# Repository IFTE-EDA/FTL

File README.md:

## Notice

This program is currently in development state. No documentation or support is available.
But this is hopefully going to change in the future (:

#### FTL
FTL (*"Fold the line"*) is a program developed to turn flat circuit layouts done in KiCad into 3D models and bend them.
The exported geometries can be used to do simulations, measure dimensions, design enclosures etc.

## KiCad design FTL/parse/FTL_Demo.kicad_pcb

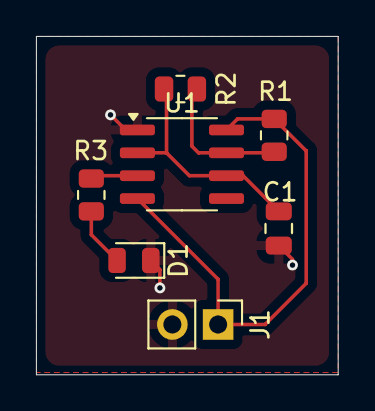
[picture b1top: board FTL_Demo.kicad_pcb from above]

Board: 2 copper layers, 16.8 x 18.8 mm, 7 parts (0 on the bottom side), 6 nets.

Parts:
C1: 10u; C_0805_2012Metric
D1: LED; LED_0805_2012Metric
J1: Conn_01x02_Pin; PinHeader_1x02_P2.54mm_Vertical
R1, R2: 100k; R_0805_2012Metric
R3: 1k; R_0805_2012Metric
U1: NE555D; SOIC-8_3.9x4.9mm_P1.27mm

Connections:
+5V: J1.1, R1.1, U1.4 (R), U1.8 (VCC)
GND: C1.2, D1.1 (K), J1.2, U1.1 (GND)
unnamed: D1.2 (A), R3.2
unnamed: R1.2, R2.1, U1.7 (DIS)
unnamed: R3.1, U1.3 (Q)
unnamed: C1.1, R2.2, U1.2 (TR), U1.6 (THR)

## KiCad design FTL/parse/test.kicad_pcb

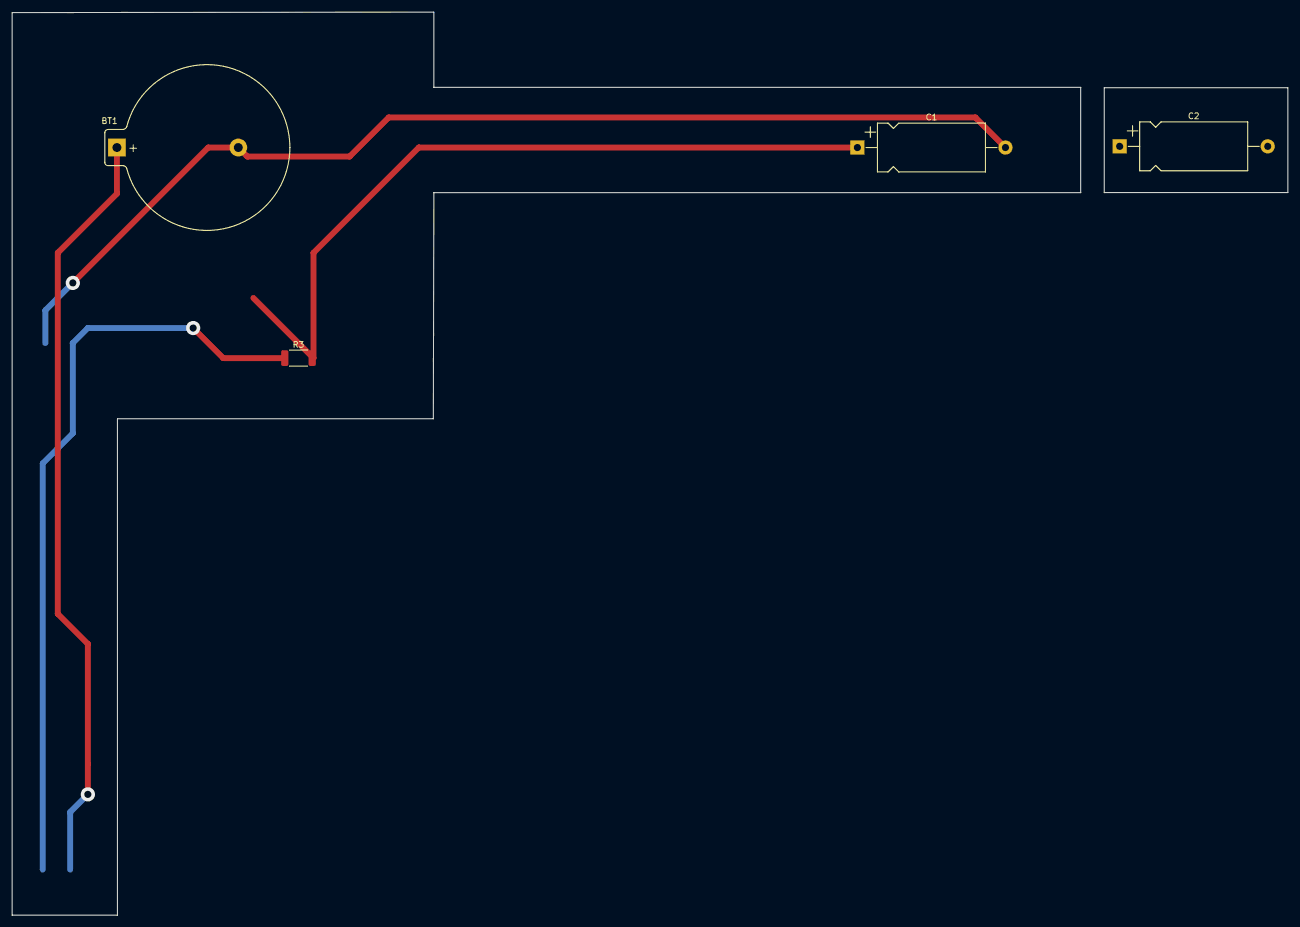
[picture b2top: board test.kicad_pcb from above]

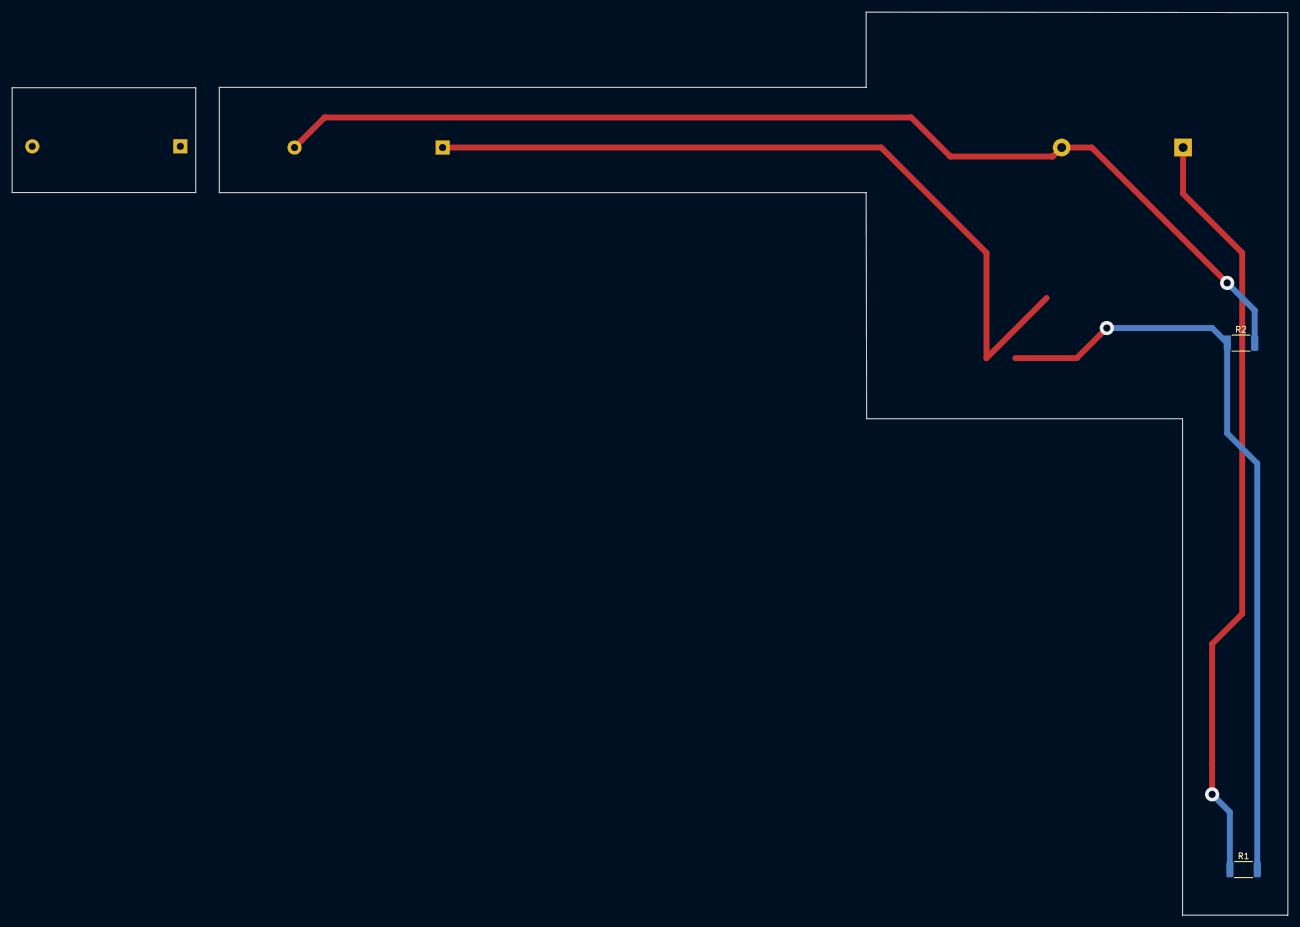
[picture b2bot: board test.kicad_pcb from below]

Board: 2 copper layers, 180.4 x 152.5 mm, 6 parts (2 on the bottom side), 4 nets.

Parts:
BT1: Battery_Cell; BatteryHolder_Keystone_105_1x2430
C1, C2: C; CP_Axial_L18.0mm_D8.0mm_P25.00mm_Horizontal
R1, R2, R3: R; R_2010_5025Metric

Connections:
unnamed: BT1.1 (+), R1.1
unnamed: BT1.2 (-), C1.2, R2.2
unnamed: C1.1, R3.2
unnamed: R1.2, R2.1, R3.1

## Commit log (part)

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2023-09-26 Update .gitlab-ci.yml file
2023-09-26 Implement transformation testing via pytest
2023-09-26 remove path manager test
2023-09-26 Daily
2023-09-26 path adress update
2023-09-26 path update
2023-09-27 Update paths
2023-09-27 Correct Path
2023-09-27 add tox
2023-09-27 Tox update
2023-09-27 Update tox
2023-09-28 Break tests
2023-09-28 Fix test
2023-09-28 Fix test data
2023-09-28 Add test debug data
2023-09-28 Update testing
2023-09-28 Fix testing
2023-09-28 Fix tests
2023-09-29 update junit suite names
2023-09-29 test
2023-09-29 tox update flake8
2023-09-29 Add flake8 functionality
2023-09-29 Update pathmanager test to pathlib
2023-09-29 fix flake8 & coverage
2023-09-29 update coverage testing
2023-10-04 Restructure the project
    Implement testing via pytest and tox
    directory structure change
    Gitlab CI
    Test coverage
    Testing data
    Bugfixing
2023-10-04 Add testing for FileParser.calculate_assignments()
2023-10-04 Fix testing, add pytest-order
2023-10-30 Remove PyQt5 dependency
2023-11-27 Done. Move to dev later.
2023-12-12 Fix 'Self' import; will correct typing later. TODO!
2023-12-12 Fix shapely-affinity problem
2024-02-22 Start Vedo Fix
2024-02-26 Initial
2024-07-25 Reorganization
2024-07-26 Add test
2024-07-26 Add Tests for FPCLayer
2024-07-26 Correct whitespace at file end
2024-07-26 Correct tox.ini
2024-07-26 Change pytest path
2024-07-26 Add Material Test
2024-07-29 Add Geometry classes
2024-07-29 Add Tests for Geometry classes
2024-07-29 Annotate class
2024-07-29 Add 3D Geom functions
2024-07-29 Add 3D Geom tests
2024-07-29 Remove v.show() causing tests to fail in headless mode
2024-07-29 Integrate nested Geom2D into Geom3D
2024-08-01 Migrate Geom2D.polygons to shapely
2024-08-01 Tidy up fcad_pcb
2024-08-01 Add support for circles
2024-08-01 Remove MainWindow-Dependency
2024-08-02 Correct FTLGeom2D.make_compound()
2024-08-02 Add class method get_circle()
2024-08-02 Correct z shift for extrusion
2024-08-02 Correct FTLGeom2D.get_circle() method
2024-08-06 Add support for: - creating rectangles - rotation - cutouts
2024-08-06 Add uspport for ellipses
2024-08-06 restructure
2024-08-07 Add support for 'roundrect' shapes
2024-08-07 Reorder
2024-08-07 Add support for arcs
2024-08-07 Extend "add_line" to support linestrings
2024-08-07 Fix FTLGeom2D.plot() for displaying overlapping polygons
2024-08-08 Remove debug outputs
2024-08-08 Add logger class with auto-indenting Mixin
2024-08-08 Add KiCAD SEXP parsing module from realthunder
2024-08-09 Test files for kicad parser
2024-08-09 Add layer list, prepare structured parsing
2024-08-09 Fix polygon creation from list + add tests
2024-08-12 Add test file for KiCAD rendering
2024-08-12 Implement layered rendering for parts and vias
2024-08-12 Implement possibility to give titles for FTLGeom2D plots
2024-08-12 Imnplement drilling
2024-08-13 Imnplement drilling to pads, utility< functions in KiCADStackupManager
2024-08-13 Make methods daisy-chainable
2024-08-13 Add tests for KiCADStackupManager
2024-08-13 Tidy up, correct rendering mistakes with single elements
2024-08-13 Add support for symbolic arcs
2024-08-13 Fix arc drawing
2024-08-14 Add Zone support
2024-08-15 Add functions to orient polys before adding
2024-08-15 Implement algorithm for poly conversion (KiCAD->Shapely)
2024-08-15 Change new layer names to "Unnamed Layer"
2024-08-20 Add colors
2024-08-20 Fix rendering problems with missing vertices
2024-08-20 Fix vertex lists
2024-08-21 Change imports to fix tests
2024-08-22 Add module
2024-08-22 Change imports
2024-08-22 Change path
2024-08-22 Update pythonpath
2024-08-22 Fix testcase
2024-08-22 Remove VMeshTools submodule
2024-08-22 remove fcad_pcb_ftl
2024-08-22 Change tox pythonpath
2024-08-22 Exclude submodules from linter
2024-08-22 Exclude .tox from linter
2024-08-27 Refactor Geometry classes, add ABC
2024-08-27 Add ABC for 3D Geometry
2024-08-27 Move tests
2024-08-27 Add GMSHGeometry and test suite; Implement Polygons, Rectangles and circles
2024-08-27 Update requirements to GMSH
2024-08-27 Install libglu1
2024-08-28 Install gmsh
2024-08-28 Install libglu1-mesa
2024-08-28 Update image
2024-08-28 Remove post-build libglu1-mesa install
2024-08-28 Implement ellipses and RoundedRects
2024-08-28 Implement Ellipses & RoundedRects
2024-08-28 Implement Lines
2024-08-28 Implement Arcs
2024-08-28 Implement Cutouts
2024-08-28 Cleanup, Implement Translation
2024-08-28 Implement Rotation
2024-08-28 Implement Extrusion
2024-08-29 Implement unfused extruding + tests
2024-08-29 Implement GMSHGeom3D tests and len() for 2D and 3D geoms
2024-08-29 Improve Object adding + implement _dimtags
2024-08-29 Add dimension parameter to GMSHGeom2D.render()
2024-09-02 Implement GMSHGeom2D.copy() and selective layer rendering
2024-09-02 Make GMSHGeom2D.plot() only show contained geometries
2024-09-02 Fix rounded rect rendering
2024-09-03 Fix KiCADParser for GMSHGeom2D
2024-09-03 Add status message argument to GMSHGeom2D.plot()
2024-09-03 Implement 3D compounds
2024-09-04 Implement setting visibility
2024-09-05 Mesh fragmenting test
2024-10-01 Fix node orientation for zones
2024-10-01 New testing file
2024-10-01 Add new test file
2024-10-02 Enable gr_line and gr_arc rendering and filling the "Edge.Cuts" layer
2024-10-02 Add new testing file
2024-10-07 Add Implement bulging to comply with DXF files
2024-10-08 Correct typo
2024-10-08 Generate test files for dxf
2024-10-08 Add testing for DXFParser
2024-10-08 Add test file for circles
2024-10-09 Add arc and thickness test data
2024-10-09 Implement width rendering for single segments of a polyline ! not working, recursion error
2024-10-10 Enable DXF parsing
2024-10-11 Reverse Implementation of lines with changing width
2024-10-11 Fix paths in tests
2024-10-11 Update tox for test file generation
2024-10-11 Add ezdxf to requirements
2024-10-11 Update test structure
2024-10-11 Update test generation script
2024-10-14 Create test data for all testcases
2024-10-14 Add hint for unsupported segment width
2024-10-14 Tidy up
2024-10-14 Add tests for KiCadParser
2024-10-14 Add test file for layers
2024-10-14 Convert tuples to lists for compliance
2024-10-14 Add KiCadLayer tests
2024-10-14 Add KiCadObject, KiCadEntity, KiCadRect, KiCadFilledPolygon tests
2024-10-14 Correct initialization of derivative objects
2024-10-14 Add tests for KiCadArc, KiCadLine and KiCadPoly
2024-10-14 Fix parameter fetching
2024-10-14 Add TCs for KiCadPart
2024-10-14 Exclude optimistic tests. Need to change main code first
2024-10-15 Add anotation for further changes
2024-10-15 Add tests for KiCadVia and KiCadPad
2024-10-15 Rename
2024-10-15 Add TCs for KiCad Object rendering
2024-10-16 Close poly in KiCadRect constructor
2024-10-16 Fix points
2024-10-16 Fix parameters
2024-10-16 Remove duplicate start/endpoints in polys generated from lists
2024-10-16 Remove phantom points in bulged polygons
2024-10-16 Remove unecessary debug output
2024-10-17 Update tests to test for points
2024-10-17 Remove plotting functions to fix testing pipeline
2024-10-17 Remove whitespace
2024-10-17 More tests
2024-10-17 Fix multiple points problem in geometries
    Squashed commit of the following:
    commit bf5ac210e43efda0dac97f902c8ddddecf6306b1
    Author: nico-arnold <82146516+nico-arnold@users.noreply.github.com>
    Date: Thu Oct 17 16:26:57 2024 +0200
    More tests
    commit a29f86d60b3fef1d87a924961cf4152bd11a50ce
2024-10-18 Create empty layer test file
2024-10-18 Remove risc of double endpoints
2024-10-18 Test data for stackup parsing/rendering
2024-10-18 Move file
2024-10-18 Extend tests
2024-10-18 Remove submodule 'PyUNV'
2024-10-18 Add testing data
2024-10-18 Make Flake8 conform
2024-10-21 Remove comments
2024-10-21 Start Fix for open polygons
2024-10-22 Join open polygons
2024-10-22 Add test data for assembling open polys
2024-10-23 Finisjh tests for open 2-part polygons
2024-10-23 Implement automatic polygon fixing
2024-10-23 Fix testing, add 3-part poly fixing tests
2024-10-23 Add scipy
2024-10-25 Move open poly tests to integration tests
2024-10-28 Add test data for bulged poly assembly
2024-10-29 Fix open poly matching
2024-10-29 Tests for 3-part open poly matching
2024-10-29 Remove debug plot
2024-10-29 Add TCs for duplicate points
2024-10-29 Fix bug for endpoint comparison
2024-10-29 Fix Error when rendering closed lines
2024-10-29 Fix comparisons
2024-10-29 Add snapping of poly endpoints + TCs
2024-10-30 Add "extrude" method for DXFLayer
2024-11-04 Undo test
2024-11-04 Reverse Stackup order Add support for multi-layer drilling
2024-11-04 Reverse Stackup order
2024-11-04 Finish drill test
2024-11-04 3D tests for drills
2024-11-04 2D test for vias
2024-11-05 Fix data for pads
2024-11-22 Implement "fragment"
2024-11-22 Implement "fragment" tests
2024-11-22 Implement touching parts fragmenting test
2024-11-22 Add support and tests for fetching top layers of extrusions
2024-11-25 Add proof-of-concept for fragmenting with physical groups
2024-11-26 Start support for physical groups and fragmenting
2024-11-27 Implement physical groups + tests
2024-11-27 Implement physical groups for 2D + tests, add DimensionError
2024-11-27 Add tests for physical group coexistence
2024-11-27 Rename "make_compound" to "make_fusion"
2024-11-28 Add support for compounds
2024-11-29 Add support for rotating and translating compounds
2024-12-02 Test if physical groups adjust to compounds
2024-12-02 Implement entity fetching for physical groups
2024-12-04 Enable nested renumbering for elements that were cut apart from a compounding operation
2024-12-06 Implement "ripup" for GMSHGEOM2D/3D + tests
2024-12-06 Implement GMSHPhysicalGroup.delete(), uncommit(), delete_all() + tests
2024-12-09 Fix deletion tests
2024-12-10 Implement GMSHPhysicalGroup.uncommit_all()
2024-12-10 Add test for create_group_solid()
2024-12-10 Add create_group_solid()
2024-12-12 Implement Elmer body generation + tests
2024-12-16 Fix minor bug, rename create_group_surface to create_group_boundary
2024-12-18 Add GMSHConfig class, add failing test forcreating physical groups on structured surfaces
2024-12-18 Add test file for mesh structuring & transformation
2024-12-18 Adjust dimensions
2024-12-18 Benchmark for geometry generation
2024-12-18 Move group creation
2024-12-18 Get surfaces by selecting via bounding box
2024-12-18 Get top surfaces via boundary selection
2024-12-18 Implement GMSHGeom3D.surface via bounding box query
2024-12-18 Fix return type
2024-12-18 Fix & activate xfailing test
2024-12-20 Change for transforming mesh via existing "Transformation" classes
2024-12-20 Start changing old transformation classes for the use with new interfaces
2025-01-06 Implement classes for parsing nested polygons in DXF import
2025-01-07 Swap polygons and holes if they are contained in a new polygon
2025-01-08 Parse nested polygons as polys with holes
2025-01-08 Add simple tests for polygons with holes
2025-01-08 Add more complex tests for nested polys
2025-01-09 Add debug info, remove typos
2025-01-14 Debug info
2025-01-15 Remove auto-reversing of polies, add debug info, change bulge index in point arrays from 4 to 2
2025-01-15 Add debug info
2025-01-16 Add final polygon dump as debug
2025-01-16 Fix nesting; add debug information
2025-01-20 Change line width from ".thickness" to the correct ".lineweight"
2025-01-20 Add model creator for Microstrip sim usecase test
2025-01-21 Prepare for 0-width-lines
2025-01-21 Sync before PhysicalGroup.commit_all()
2025-02-19 Add group creation and renumbering to GMSHGeom2D
2025-03-17 Add support to translate along z-axis
2025-03-27 New version of DirBend without rotating whole model
2025-03-27 Combine matrices
2025-04-04 Finalize & add DirBendNew; TODO: optimize
2025-04-04 Revert to original after testing changes
2025-04-14 Enable YAML description for technologies
2025-04-14 Add support for adding geometries to GMSHGeom2D
2025-04-14 Remove debug output
2025-04-14 Add variable system
2025-04-14 Test file for YAML parsing
2025-04-16 Sync gmsh before committing groups; start work on pads + labeling
2025-04-17 Enable returning new geometries instead of rendering into existing ones
2025-04-17 Add bounding box property
2025-04-17 Deactivate test to be implemented in the future - xfail for now
2025-04-23 Fix surface fetching for geometries
